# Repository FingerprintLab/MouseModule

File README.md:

# MouseModule

This is an eurorack module that processes mouse events through the [Raspberry Pi Zero](https://www.raspberrypi.org/documentation/hardware/raspberrypi/spi/README.md) and [MCP4922](http://ww1.microchip.com/downloads/en/DeviceDoc/22250A.pdf) and outputs 2 CV signals (for the X and Y coordinates) a GATE signal (controlled by the left button) and a TRIGGER signal (controlled by the roght button). It has also recording and playback capabilities with more complex mice.  

## Hardware

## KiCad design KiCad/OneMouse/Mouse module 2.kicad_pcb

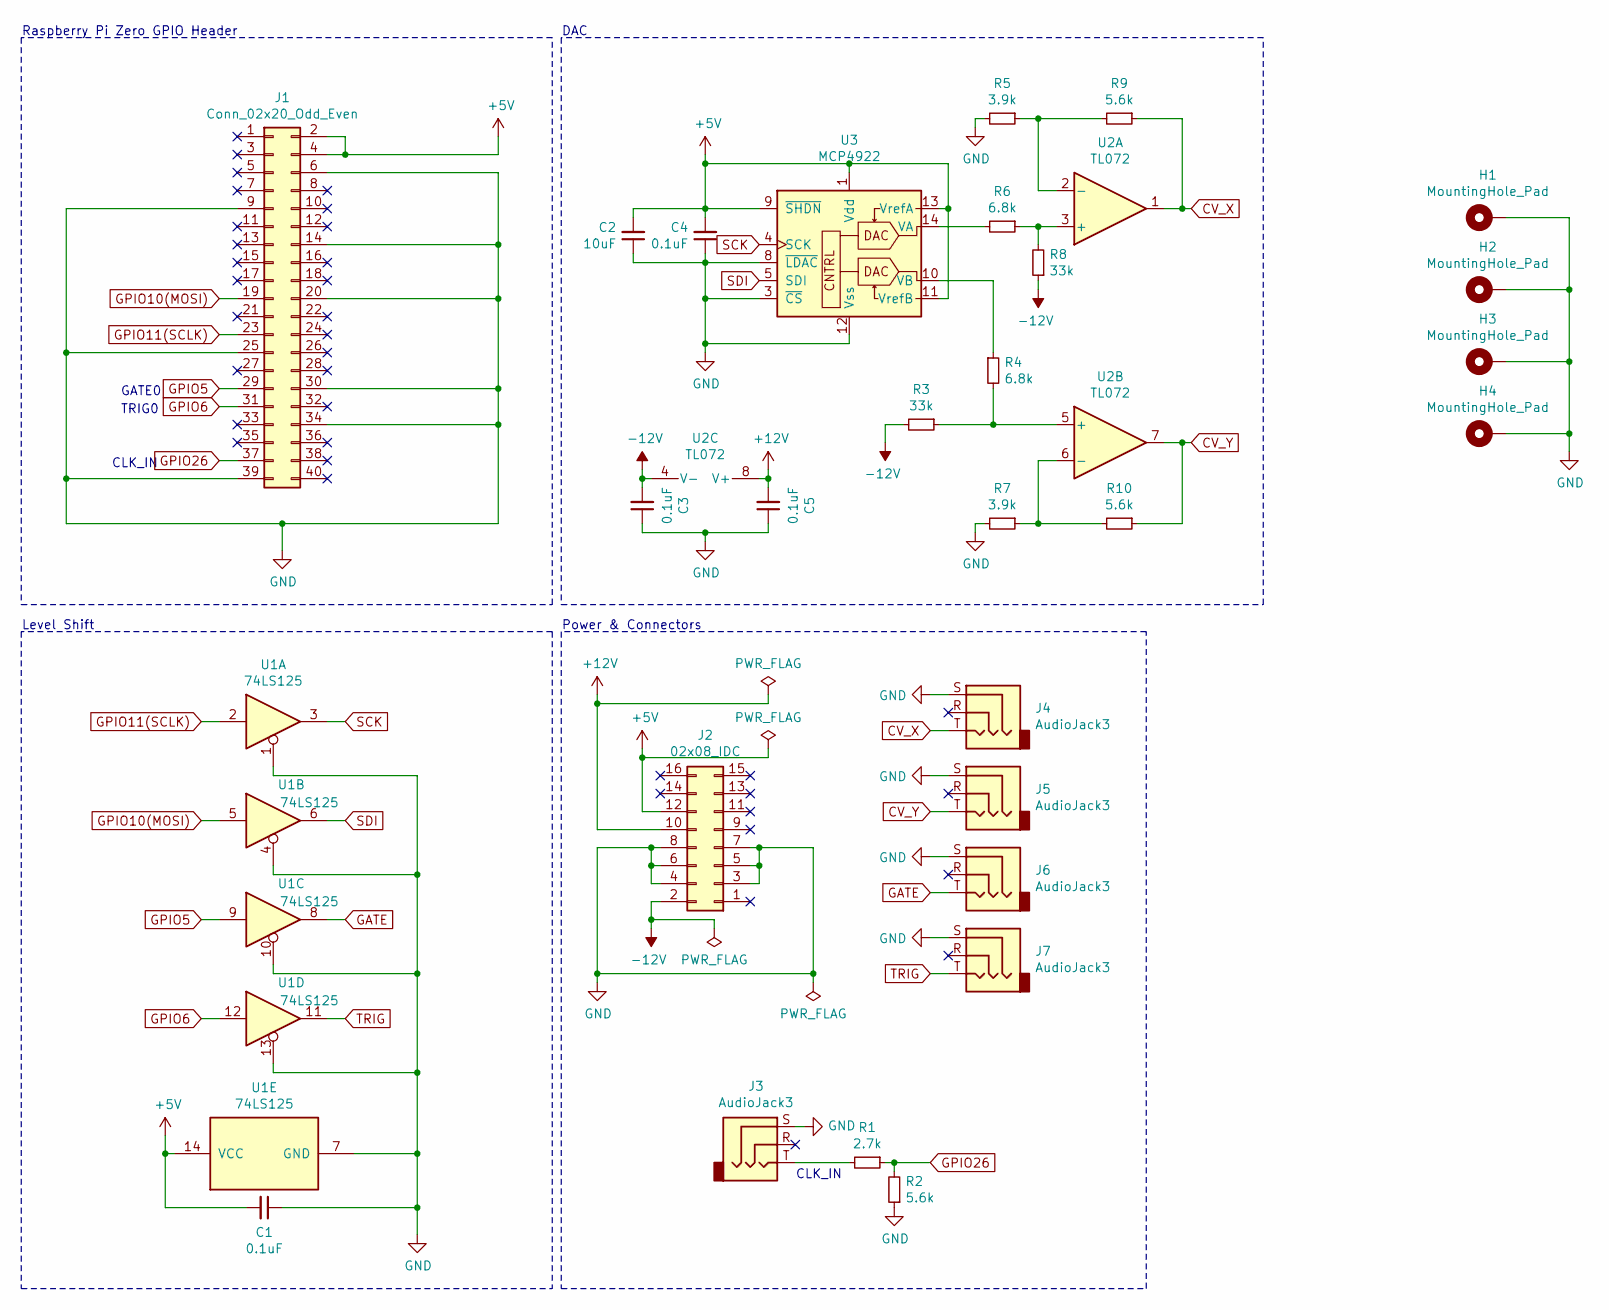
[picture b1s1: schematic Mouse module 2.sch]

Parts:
C1, C3, C4, C5: 0.1uF; C_Disc_D4.7mm_W2.5mm_P5.00mm
C2: 10uF; C_Disc_D4.7mm_W2.5mm_P5.00mm
H1, H2, H3, H4: MountingHole_Pad; MountingHole_2.7mm_Pad
J1: Conn_02x20_Odd_Even; PinSocket_2x20_P2.54mm_Vertical
J2: 02x08_IDC; IDC-Header_2x08_P2.54mm_Vertical
J3, J4, J5, J6, J7: AudioJack3; CUI_SJ1-3533
R1: 2.7k; R_Axial_DIN0207_L6.3mm_D2.5mm_P10.16mm_Horizontal
R2, R9, R10: 5.6k; R_Axial_DIN0207_L6.3mm_D2.5mm_P10.16mm_Horizontal
R3, R8: 33k; R_Axial_DIN0207_L6.3mm_D2.5mm_P10.16mm_Horizontal
R4, R6: 6.8k; R_Axial_DIN0207_L6.3mm_D2.5mm_P10.16mm_Horizontal
R5, R7: 3.9k; R_Axial_DIN0207_L6.3mm_D2.5mm_P10.16mm_Horizontal
U1: 74LS125; DIP-14_W7.62mm_Socket
U2: TL072; DIP-8_W7.62mm_Socket
U3: MCP4922; DIP-14_W7.62mm_Socket

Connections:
+5V: C1.2, C2.2, C4.2, J1.2, J1.4, J2.12, U1.14 (VCC), U3.1 (Vdd), U3.9 (~SHDN), U3.11 (VrefB), U3.13 (VrefA)
+12V: C5.2, J2.10, U2.8 (V+)
-12V: C3.2, J2.2, R3.2, R8.1, U2.4 (V-)
CV_X: J4.T, R9.1, U2.1
CV_Y: J5.T, R10.1, U2.7
GATE: J6.T, U1.8
GND: C1.1, C2.1, C3.1, C4.1, C5.1, H1.1, H2.1, H3.1, H4.1, J1.6, J1.9, J1.14, J1.20, J1.25, J1.30, J1.34, J1.39, J2.3, J2.4, J2.5, J2.6, J2.7, J2.8, J3.S, J4.S, J5.S, J6.S, J7.S, R2.1, R5.2, R7.2, U1.1, U1.4, U1.7 (GND), U1.10, U1.13, U3.3 (~CS), U3.8 (~LDAC), U3.12 (Vss)
GPIO5: J1.29, U1.9
GPIO6: J1.31, U1.12
GPIO10(MOSI): J1.19, U1.5
GPIO11(SCLK): J1.23, U1.2
GPIO26: J1.37, R1.1, R2.2
unnamed: J3.T, R1.2
unnamed: R3.1, R4.2, U2.5 (+)
unnamed: R4.1, U3.10 (VB)
unnamed: R5.1, R9.2, U2.2 (-)
unnamed: R6.1, R8.2, U2.3 (+)
unnamed: R6.2, U3.14 (VA)
unnamed: R7.1, R10.2, U2.6 (-)
SCK: U1.3, U3.4 (SCK)
SDI: U1.6, U3.5 (SDI)
TRIG: J7.T, U1.11

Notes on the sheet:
Level Shift
Power & Connectors
DAC
Raspberry Pi Zero GPIO Header
CLK_IN
GATE0
TRIG0

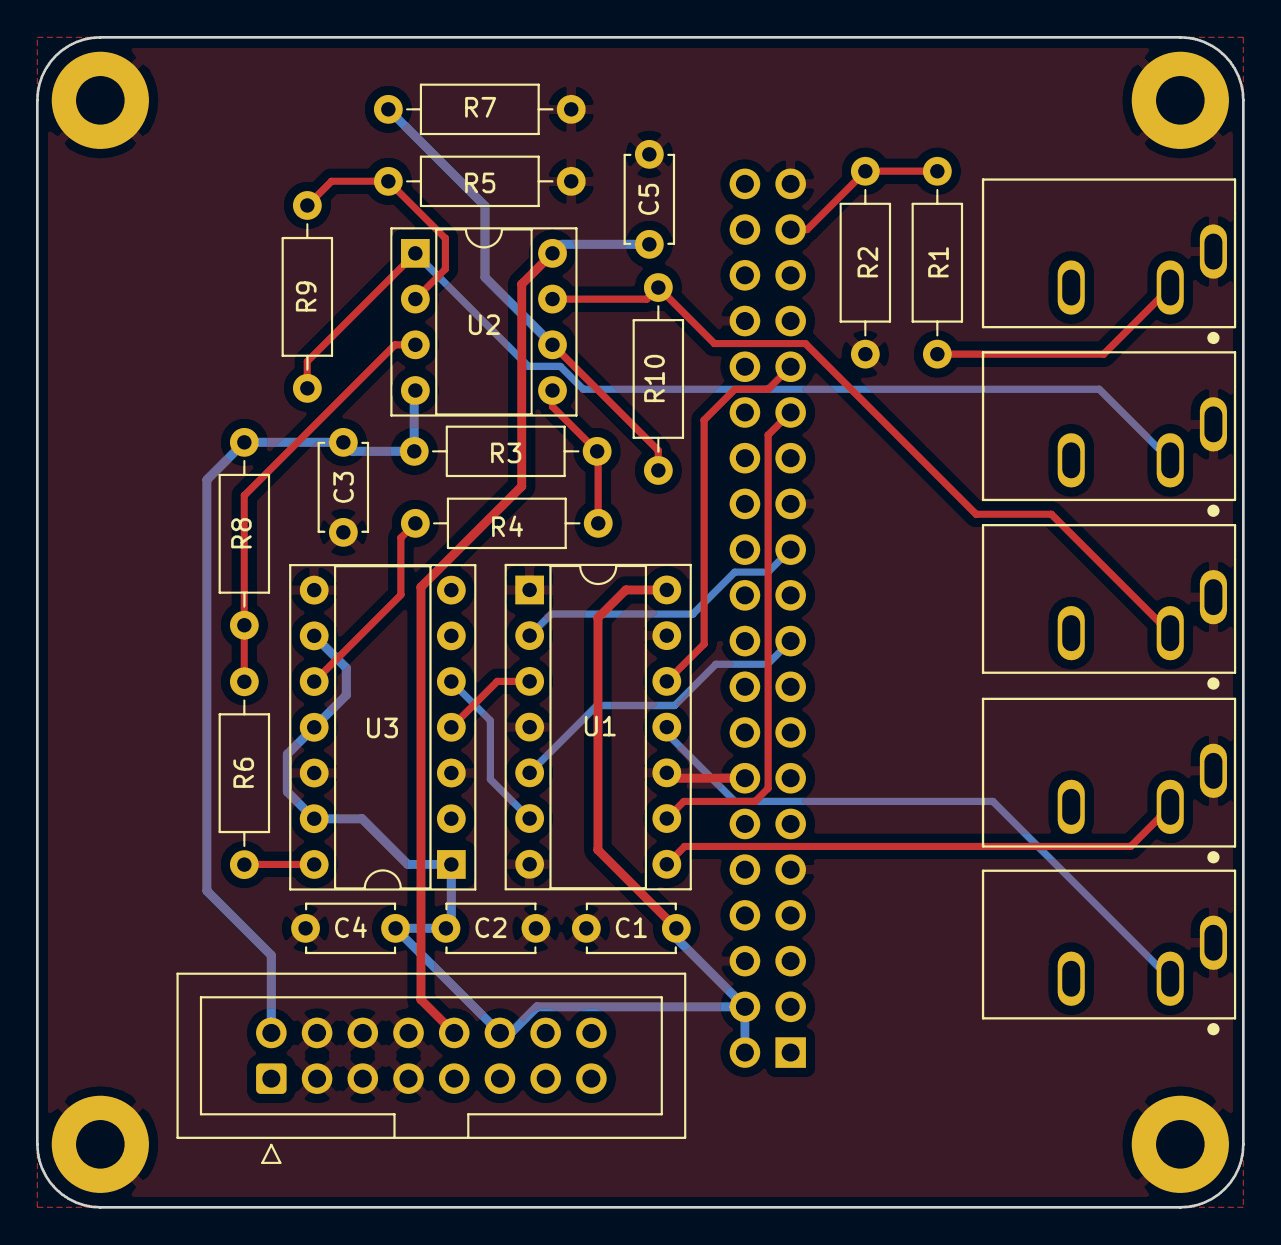
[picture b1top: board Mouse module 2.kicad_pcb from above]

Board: 2 copper layers, 67.0 x 65.0 mm, 29 parts (1 on the bottom side), 22 nets.

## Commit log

2020-10-21 Add files via upload
    main python script
2020-10-29 Rename MouseModule.py to Software/MouseModule.py
2020-11-03 New schematic
2020-11-03 Included new schematic
2020-11-12 initial commit of one mouse version
2020-11-13 undate README
2020-12-08 Resolved wheel event issue
2020-12-09 Changed playback to erase
2020-12-09 ISSUE: relative axes movements can't be monitored
2020-12-09 Mouses corrected with mice
2021-01-06 current library update
2021-01-14 js implementation
2021-01-14 first attempt on linux
2021-01-15 update instructions for JS
2021-01-16 mouse buttons recognized
2021-01-16 added shell script
2021-01-16 all events detected
2021-01-16 random commit
2021-01-16 identation correction
2021-01-16 started js functions
2021-01-16 pointer div
2021-01-16 working on playback
2021-01-17 basic playback
2021-01-17 raw graphical representation
2021-01-18 event handling
2021-01-18 playback event handling
2021-01-19 first WSL commit
2021-01-21 first testbranch commit
2021-01-21 added new-file
2021-01-21 JS directory updated
2021-01-21 script.js updated
2021-01-21 script updated
2021-01-21 live debugging
2021-01-21 minor update
2021-01-22 first rpio experiment
2021-01-23 deleted node files
2021-01-23 renamed server.js to app.js
2021-01-23 added .gitignore
2021-01-23 removed python files
2021-01-23 updated .gitignore
2021-01-23 added node dependecies
2021-01-23 deleted useless test file
2021-01-24 added body-parser
2021-01-24 renaming
2021-01-24 client-server communication
2021-01-24 deleted 2 mice hardware version
2021-01-24 first trigger attempt on server
2021-01-24 first gate attempt on server
2021-01-24 client refinement
2021-01-25 gate & trigger working
2021-01-25 changed trigger pulse
2021-01-28 PWM test
2021-02-21 general cleaning
2021-02-21 added npm start comand
2021-02-21 commented out the server and added sin function
2021-02-21 .gitignore corrected
2021-02-21 pwm example
2021-02-26 tweaking pwm example
2021-02-26 cleaned repository
2021-03-03 first linuxC commit
2021-03-03 removed JS folder
2021-03-03 removed usless files and folders
2021-03-03 cleaned branch
2021-03-03 removed .vscode folder
2021-03-03 update README and hardware image
2021-03-03 updated README and images
2021-03-03 corrected typo
2021-03-04 removed useless folder
2021-03-04 added type macro
2021-03-04 removed executable to avoid compatibility issues
2021-03-04 added makefile
2021-03-04 added human readable names to types and codes
2021-03-04 added argument
2021-03-05 fixed strcmp usage
2021-03-06 added functional printfs
2021-03-06 added more info in printFunctional
2021-03-06 added basic event handlers
2021-03-06 first recording commit
2021-03-06 added getline example
2021-03-06 removed test.txt
2021-03-06 added recording functions
2021-03-07 fixed eventSearch.c
2021-03-07 first forking commit
2021-03-07 removed getLine.c
2021-03-07 removed eventSearch.c
2021-03-07 added filename detection & basic multithreading
2021-03-08 removed the linux_input.c example
2021-03-08 added playback thread
2021-03-08 changed the project file structure
2021-03-08 created dummy signals header file
2021-03-08 swtched mouse file
2021-03-10 changed filename 'analog.h' -> 'hw.h'
2021-03-10 only recorded events are handled in playback mode
2021-03-11 changed index type to unsigned long
2021-03-11 added some test files
2021-03-11 modified .gitignore
2021-03-11 removed Software directory
2021-03-20 position based on relative axis events
2021-06-16 PWM integrated succesfully
2021-06-16 removed DAC from schematics
2021-06-22 fixed movement issue in playback
2021-06-30 fix recording issue
2021-06-30 fixed 'width/height not defined' issue
2021-07-03 minor fixes
